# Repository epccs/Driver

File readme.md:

# Driver Circuits

From <https://github.com/epccs/Driver/>

## Overview

This is a collection of circuit boards. If you have questions consider posting an issue.

[RPUbus](https://rpubus.org)

[OrderForm](https://rpubus.org/Order_Form.html)

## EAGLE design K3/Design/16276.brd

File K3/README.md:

# K3 Hardware

## Overview

This latching solenoid driver board has three half H-bridge and a common half H-bridge that can be used to discharge a (9V/12V/24V) capacitively stored charge into a latching Solenoid coil. A current limited (300mA pk) boost converter (MC34063A) is on board to build up the stored charge from a low voltage (5V) supply.

Latching solenoids are driven with a current pulse that should last a short duration. The pulse from this driver flows in a single coil (don't use with multi-coil solenoids) and establishes a magnetic field that throws the solenoid into either a SET position or a RESET position. The pulse duration hopefully avoids overheating the coils. The Laplace force will not happen unless another magnetic field is present to act on, and will not convert electrical power into mechanical unless the force results in motion. The thrown solenoid also has a back emf in the driving coil.

## Inputs/Outputs/Functions

```
        Boost converter with 300mA pk input current limit.
        Boost leaves 200mA of a USB input for an Uno or ilk.
        Capacitor holds a charge for latching.
```

## Uses

```
        Single Coil Latching solenoids.
        Single Coil Latching relay.
```

# Table Of Contents

1. [Status](#status)
2. [Design](#design)
3. [Bill of Materials](#bill-of-materials)
4. [How To Use](#how-to-use)

# Status

[Options](#bill-of-materials)

```
        ^2  Done: Design, Layout, BOM, Review*, Order Boards, Assembly, Testing,
            WIP: Evaluation.
            Todo:   
            *during review the Design may change without changing the revision.
            Remove the parts that allow boost to connect to plug, just connect it with option to cut jumper.
            Use E3 to enable current source used to test for bridge short (save some power).
            Ship with C2 on pluggable header though I recommend soldering it when the current pulse is much over an Amp.
            location: 2017-3-30 Bench /w RPUno^6, RPUadpt^5.
                      2017-4-17 SxSXWall Encl /w RPUno^5, RPUadpt^4, SLP003-12U, 12V battery.

        ^1  Done: Design, Layout, BOM, Review*, Order Boards, Assembly, Testing, Evaluation.
            location: 2016-2-5 SxSXWall Encl /w RPUno^5, RPUadpt^4, SLP003-12U, 12V battery.
                      2016-4-17 Bench.
            
        ^0  location: 2016-12-1 SWall Encl /w RPUno^4, RPUadpt^4, SLP003-12U, 12V battery.
                      2016-2-4 removed, waiting in scrap bin.
                      2017-3-28 scraped (parts used on ^2).
```

Debugging and fixing problems i.e. [Schooling](./Schooling/)

Setup and methods used for [Evaluation](./Evaluation/)

# Design

The board is 0.063 thick, FR4, two layer, 1 oz copper with ENIG (gold) finish.

## Electrical Parameters (Typical)

```
input SUPPLY guidance: 4V to 7V
TBD (it is OSH)
```

## Mounting

```
        DIN rail
```

## Electrical Schematic

## Testing

Check correct assembly and function with [Testing](./Testing/)

# Bill of Materials

The BOM is a CVS file(s), import it into a spreadsheet program like LibreOffice Calc (or Excel), or use a text editor.

Option | BOM's included
----- | ----- 
A. | [BRD] 
Z. | [BRD] [SMD] [HDR] [PLUG] [DIN]

[BRD]: ./Design/16276BRD,BOM.csv
[SMD]: ./Design/16276SMD,BOM.csv
[HDR]: ./Design/16276HDR,BOM.csv
[PLUG]: ./Design/16276PLUG,BOM.csv
[DIN]: ./Design/16276DIN,BOM.csv

[Available](https://rpubus.org/Order_Form.html)

# How To Use

First a word about Latching Solenoids and Relays. They latch, so once a SET pulse is sent the physical part stays set until a RESET pulse is sent, even if power is lost. It is normally a good idea to send a reset pulse to each latch after power up to get them into a known state.

Latching Solenoids cost more but they use no power after latched, Energized DC circuits corroded quickly. 

The set pulse applies a voltage to the coil and produces a current in a direction that will cause the Laplace force to move the solenoid into that physical location. The reset pulse applies an opposite polarity to the coil. Once in the location some other force (spring, permanent magnet, air pressure... ), will hold the solenoid in that place.

For this circuit, the idea is to use one of the E3, nE2, or nE3 to DISABLE. Then change A0, A1, A2. Once A0 ... A2 have been selected the action happens when E3, nE2, and nE3 are all set active. Use the following settings:  

```
         A0 A1 A2 E3 nE2 nE1 : DESC
         X  X  X  0V X   X   : ALL DISABLED
         X  X  X  X  5V  X   : ALL DISABLED
         X  X  X  X  X   5V  : ALL DISABLED
         X  X  X  5V X   X   : ENABLE 17mA
         5V 0V 0V 5V 0V  0V  : BOOST
         0V 5V 0V 5V 0V  0V  : SET K1
         5V 5V 0V 5V 0V  0V  : RESET K1
         0V 0V 5V 5V 0V  0V  : SET K2
         5V 0V 5V 5V 0V  0V  : RESET K2
         0V 5V 5V 5V 0V  0V  : SET K3
         5V 5V 5V 5V 0V  0V  : RESET K3
```

Before a pulse can be sent the boost converter has to build a charge. Once E3 is active a 17mA current source will build up some voltage in the storage capacitor. When this is enough (somewhere between 1.2V to 2.2V) to allow the boost converter to turn on it will turn on a PMOS device to let power through and turn on the converter. If a bridge has failed then neither the PMOS or the converter will turn on (but the test current will keep flowing until E3 is disabled). If a charge does build up (as it should) then a pulse can be applied to set/reset one of the solenoids by writing A0, A1, and A2 inputs simultaneously (e.g. a port operation). It is also possible to change one pin at a time with the digitalWrite() function (from Wiring), but care must be taken to have the logic disabled (i.e. E3 = 0V) while selecting the A0/A1/A2 lines otherwise the charge is sent to the first line that changed while making the selection.

I've been using CAT5 pair to wire the coils. At nearly 5 Amps peak that may be risky but for a short duration pulse the CAT5 pair seems to work (your mileage may vary, but it is cheap and the twisted pair helps keep the pulse from generating EMI). 

When the pulse is sent the boost converter is turned off so only the charge in the storage capacitor (2200uF) is sent, this should keep things within the safe operating area of the output MOSFETS as long as at least 4 Ohms of resistance is between the bridges. Anything less than 4 Ohms allows excessive current and will eventually lead to a failure. For reference, 10 meters of CAT5 has less than 1.7 Ohm.

Solenoid options

* Orbit 58874N, 58874Z, 91592, 96120 Latching Solenoid valve (seems to work OK with 24V 50mSec pulse from 2200uF).
* Orbit 57861 Latching Solenoid replacement for AC operated valve (I do not have this, it plugs into Orbits 24V controls but most others are are using 9V).
* DIG S-305DC Solenoid & Adapters (http://www.digcorp.com/professional-irrigation-products/s-305dc-9-vdc-solenoid-adapters).
* Hunter 458200 Latching Solenoid for AC operated valve (e.g. ICV201GDC and ilk, but I do not have one, probably 9V pulse)
* Irritrol DCL Latching Solenoid for AC operated valve (e.g. 2400S and ilk, but I do not have one, probably 9V pulse)

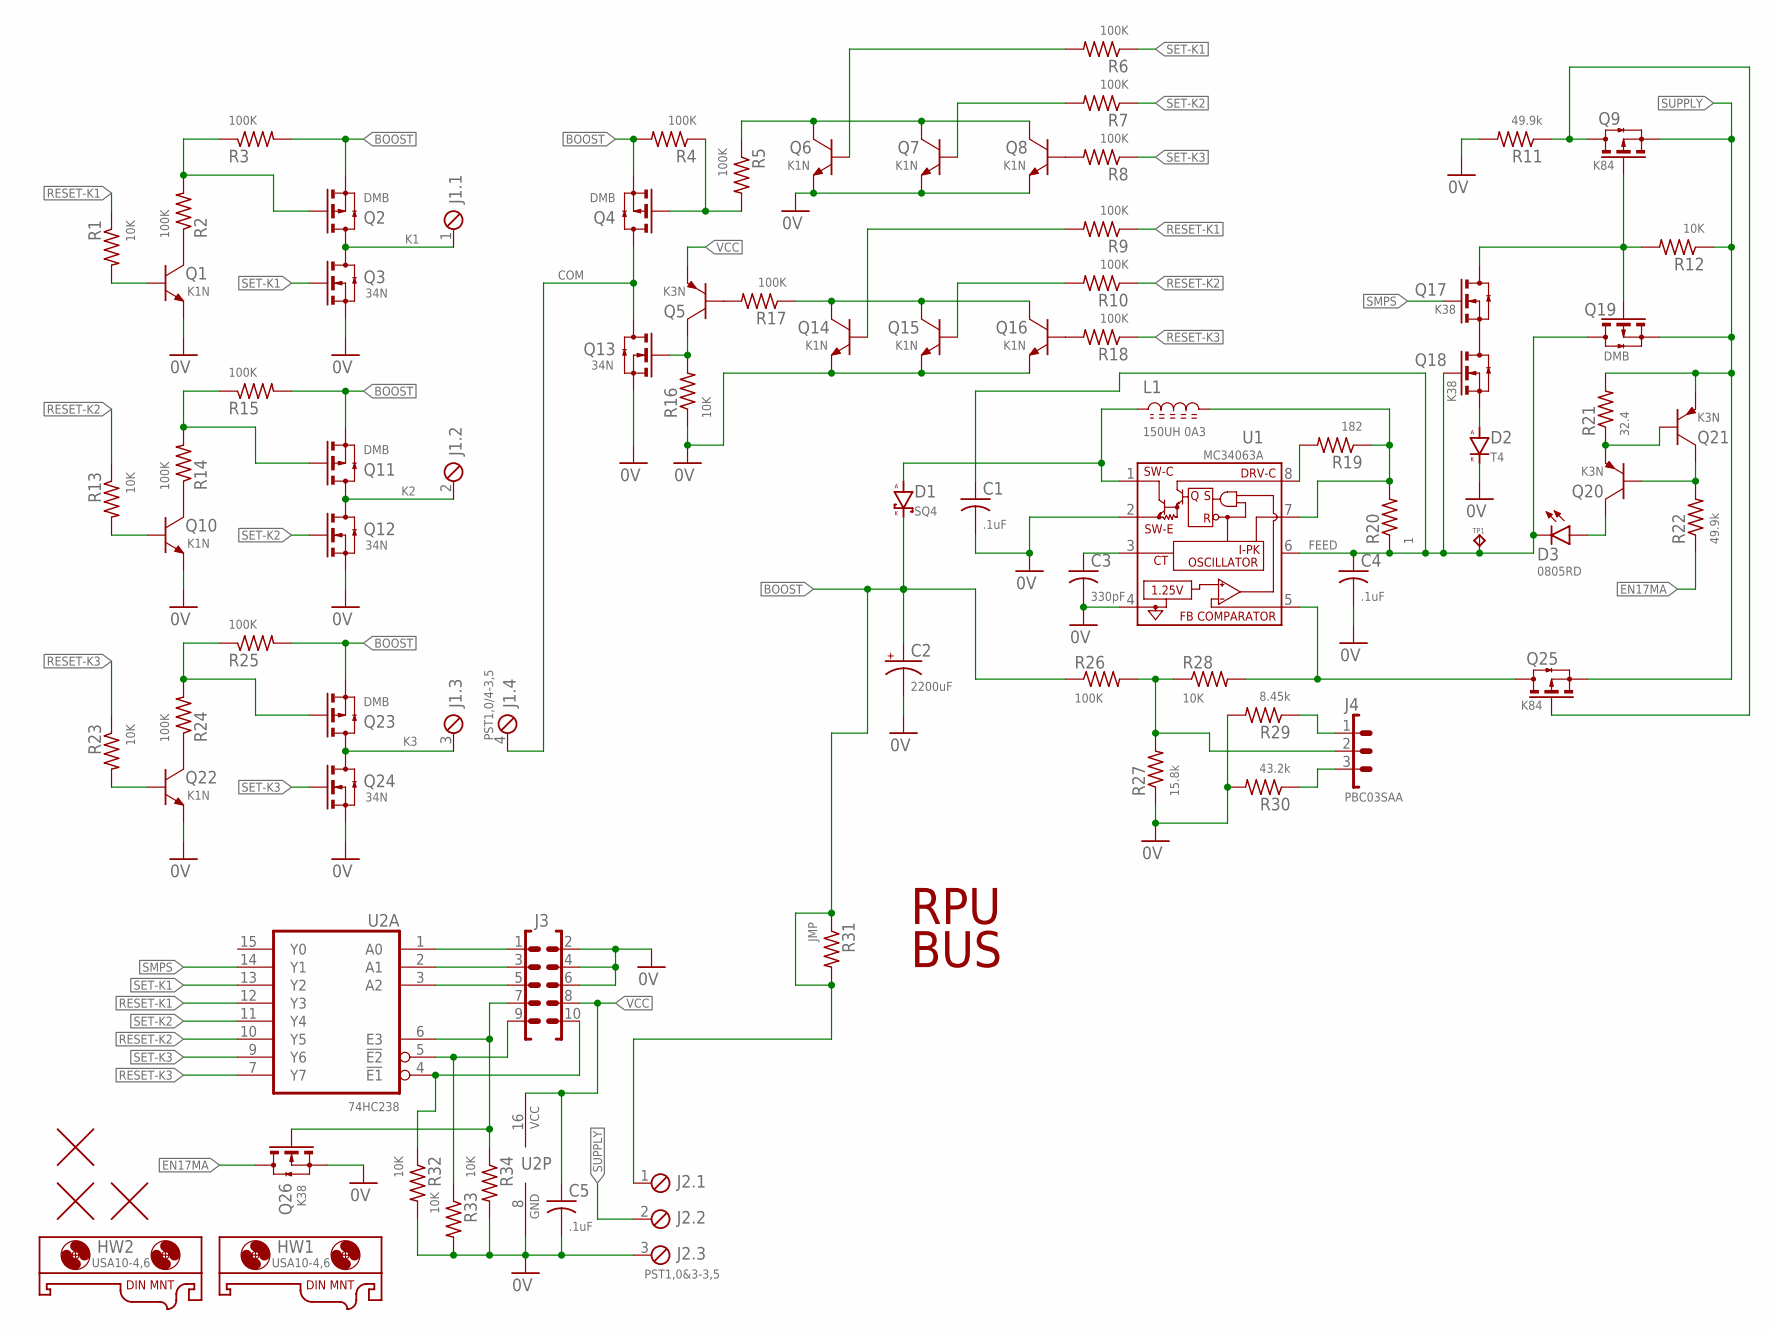
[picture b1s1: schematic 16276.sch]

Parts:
C1, C4, C5: .1uF; C0603(1608)
C2: 2200uF; E7,5-18
C3: 330pF; C0603(1608)
D1: SQ4; SMA
D2: T4; SOD123
D3: 0805RD; C0805(2012)
HW1, HW2: USA10-4,6; USA10
J1: PST1,0/4-3,5; MCV4
J2: PST1,0&3-3,5; MCV3
J3: 2X5
J4: PBC03SAA; 1X3
L1: 150UH 0A3; L2626
Q1, Q6, Q7, Q8, Q10, Q14, Q15, Q16, Q22: K1N; SOT23
Q2, Q4, Q11, Q19, Q23: DMB; SOT23
Q3, Q12, Q13, Q24: 34N; SOT23
Q5, Q20, Q21: K3N; SOT23
Q9, Q25: K84; SOT23
Q17, Q18, Q26: K38; SOT23
R1, R12, R13, R16, R23, R28, R32, R33, R34: 10K; C0805(2012)
R2, R3, R4, R5, R6, R7, R8, R9, R10, R14, R15, R17, R18, R24, R25, R26: 100K; C0805(2012)
R11, R22: 49.9k; C0805(2012)
R19: 182; C0805(2012)
R20: 1; C1210(3225)
R21: 32.4; C0805(2012)
R27: 15.8k; C0805(2012)
R29: 8.45k; C0805(2012)
R30: 43.2k; C0805(2012)
R31: JMP; C0805(2012)
TP1: TPPAD1-08; P1-08
U1: MC34063A; SOIC8
U2: 74HC238; 16SOIC
U$2, U$3, U$4: FIDUCIAL1.27; FIDUCIAL-1.27

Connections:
0V: C1.2, C2.-, C3.2, C4.2, C5.2, D2.C (K), J2.3, J3.2, J3.4, J3.6, Q1.E, Q3.2(S) (S), Q6.E, Q7.E, Q8.E, Q10.E, Q12.2(S) (S), Q13.2(S) (S), Q14.E, Q15.E, Q16.E, Q22.E, Q24.2(S) (S), Q26.2(S) (S), R11.2, R16.1, R27.1, R29.2, R30.2, R32.2, R33.2, R34.2, U1.2 (SW-E), U1.4 (GND), U2.8 (GND)
!E1: J3.10, R32.1, U2.4 (!E1)
!E2: J3.9, R33.1, U2.5 (!E2)
A0: J3.1, U2.1 (A0)
A1: J3.3, U2.2 (A1)
A2: J3.5, U2.3 (A2)
BOOST: C2.+, D1.K, J2.1, Q2.2(S) (S), Q4.2(S) (S), Q11.2(S) (S), Q23.2(S) (S), R3.2, R4.2, R15.2, R25.2, R26.1, R31.1, R31.2
COM: J1.4, Q4.3(D) (D), Q13.3(D) (D)
E3: J3.7, Q26.1(G) (G), R34.1, U2.6 (E3)
EN17MA: Q26.3(D) (D), R22.1
FEED: C1.1, C4.1, D3.K, Q18.1(G) (G), Q19.3(D) (D), R20.1, TP1.TP, U1.6 (VCC)
K1: J1.1, Q2.3(D) (D), Q3.3(D) (D)
K2: J1.2, Q11.3(D) (D), Q12.3(D) (D)
K3: J1.3, Q23.3(D) (D), Q24.3(D) (D)
unnamed: Q9.3(D) (D), Q25.1(G) (G), R11.1
unnamed: Q23.1(G) (G), R24.2, R25.1
unnamed: Q22.C, R24.1
unnamed: Q22.B, R23.2
unnamed: Q17.2(S) (S), Q18.3(D) (D)
unnamed: Q25.3(D) (D), R28.2, U1.5 (FB)
unnamed: D2.A, Q18.2(S) (S)
unnamed: Q4.1(G) (G), R4.1, R5.2
unnamed: R19.2, U1.8 (DRV-C)
unnamed: L1.2, R19.1, R20.2, U1.7 (I-PK)
unnamed: D1.A, L1.1, U1.1 (SW-C)
unnamed: C3.1, U1.3 (CT)
unnamed: Q5.C, Q13.1(G) (G), R16.2
unnamed: Q9.1(G) (G), Q17.3(D) (D), Q19.1(G) (G), R12.2
unnamed: J4.2, R26.2, R27.2, R28.1
unnamed: Q6.C, Q7.C, Q8.C, R5.1
unnamed: Q6.B, R6.2
unnamed: Q8.B, R8.2
unnamed: Q2.1(G) (G), R2.2, R3.1
unnamed: Q1.C, R2.1
unnamed: Q1.B, R1.2
unnamed: Q11.1(G) (G), R14.2, R15.1
unnamed: Q10.C, R14.1
unnamed: Q10.B, R13.2
unnamed: Q7.B, R7.2
unnamed: Q5.B, R17.2
unnamed: Q14.C, Q15.C, Q16.C, R17.1
unnamed: Q14.B, R9.2
unnamed: Q15.B, R10.2
unnamed: D3.A, Q20.C
unnamed: Q16.B, R18.2
unnamed: J4.3, R30.1
unnamed: J4.1, R29.1
unnamed: Q20.E, Q21.B, R21.1
unnamed: Q20.B, Q21.C, R22.2
RESET-K1: R1.1, R9.1, U2.12 (Y3)
RESET-K2: R10.1, R13.1, U2.10 (Y5)
RESET-K3: R18.1, R23.1, U2.7 (Y7)
SET-K1: Q3.1(G) (G), R6.1, U2.13 (Y2)
SET-K2: Q12.1(G) (G), R7.1, U2.11 (Y4)
SET-K3: Q24.1(G) (G), R8.1, U2.9 (Y6)
SMPS: Q17.1(G) (G), U2.14 (Y1)
SUPPLY: J2.2, Q9.2(S) (S), Q19.2(S) (S), Q21.E, Q25.2(S) (S), R12.1, R21.2
VCC: C5.1, J3.8, Q5.E, U2.16 (VCC)

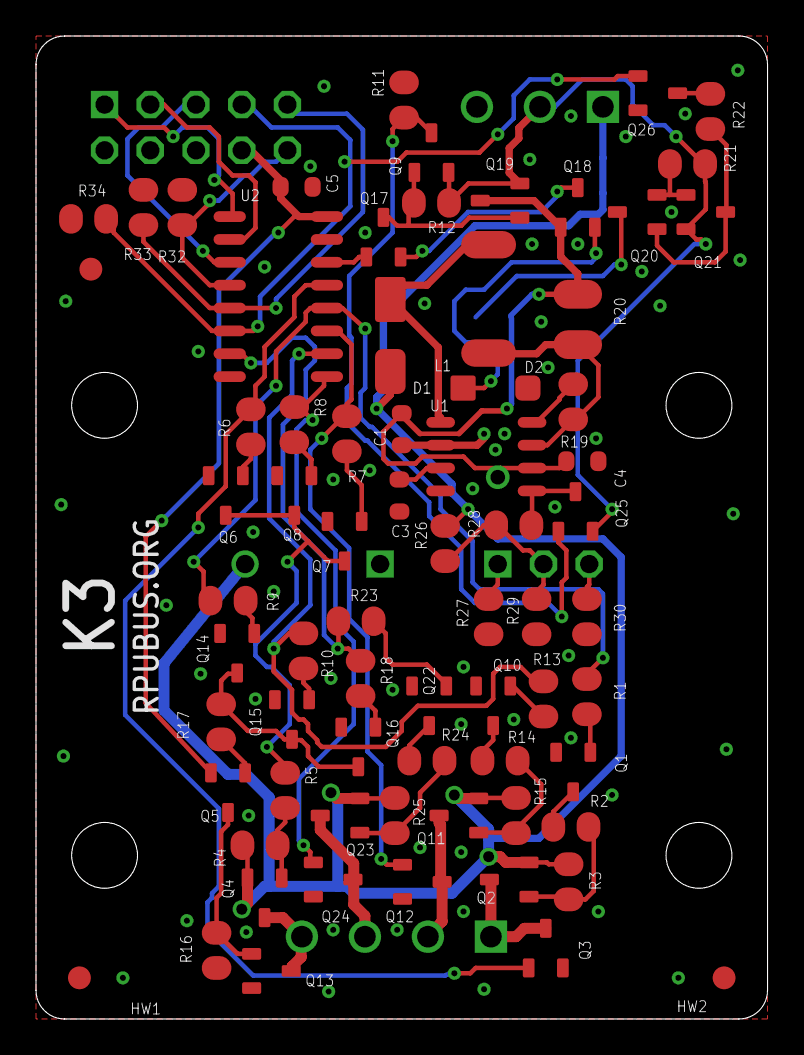
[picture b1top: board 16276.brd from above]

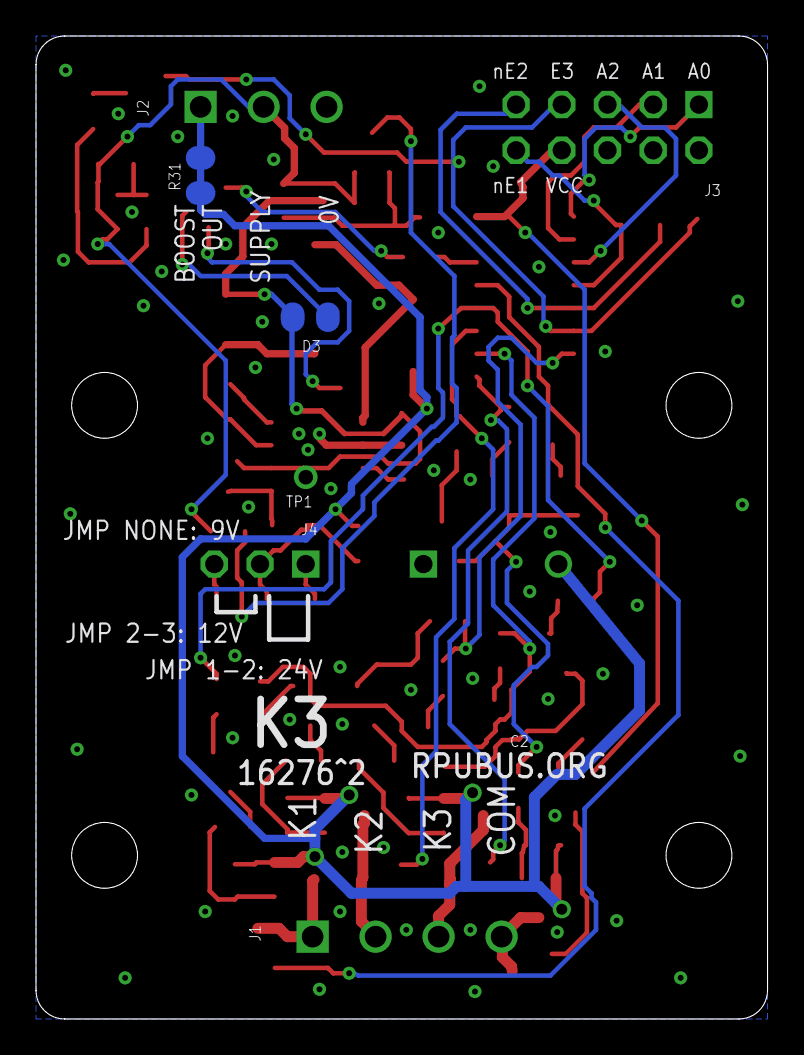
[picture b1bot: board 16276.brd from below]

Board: 2 copper layers, 40.6 x 54.6 mm, 81 parts (8 on the bottom side), 58 nets.

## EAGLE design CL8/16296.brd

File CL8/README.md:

# CL8 Hardware

## Overview

Select 1 of 8 Current Loop sensors. The sellected current  path returns current flow to a common termination (sense) resistor.

## Inputs/Outputs/Functions

```
        Input a current loop source
        Output to a loop termination resistor
        Ditital control using a 74HC238 logic IC
        Multiplex 1 of 8 sensors with a supply (current source).
```

## Uses

```
        Select one from several sensors (e.g. MT, LT, HT).
```

# Table Of Contents

1. [Status](#status)
2. [Design](#design)
3. [Bill of Materials](#bill-of-materials)
4. [How To Use](#how-to-use)

# Status

This was split out of Irrigate7 to try some ideas. The plan was to use this with the input capture (ICP3) on Irrigate7 to measure pulse timing from soil moisture sensors. However CL8 also works with regular current loops on the ADC inputs and can be used with RPUno. Irrigate7 with two pulse sensor inputs seems like a good idea, so this circuit will not be integrated back onto that board but can be used with it. 

```
        ^0  Done: Design, Layout, BOM, Review*, Order Boards, Assembly, 
            WIP: Testing (sort of on hold for now), 
            Todo: Evaluation.
            *during review the Design may change without changing the revision.
            location: 2016-11-12 Bench.
```

Debugging and fixing problems i.e. [Schooling](./Schooling/)

Setup and methods used for [Evaluation](./Evaluation/)

# Design

The board is 0.063 thick, FR4, two layer, 1 oz copper with ENIG (gold) finish.

## Electrical Parameters (Typical)

```
input SUPPLY guidance: 4V to 7V
TBD (it is OSH)
```

## Mounting

```
        DIN rail
```

## Electrical Schematic

## Testing

Check correct assembly and function with [Testing](./Testing/)

# Bill of Materials

Import the [BOM](./Design/16296,BOM.csv) into LibreOffice Calc (or Excel) with semicolon separated values, or use a text editor.

# How To Use

For this circuit, the idea is to set one of the E3, nE2, or nE3 to DISABLE. Then change A0, A1, A2. Once A0 ... A2 have been selected the action happens when E3, nE2, and nE3 are all set active. Use the following settings:  

```
         A0 A1 A2 E3 nE2 nE1 : DESC
         X  X  X  0V X   X   : ALL DISABLED
         X  X  X  X  5V  X   : ALL DISABLED
         X  X  X  X  X   5V  : ALL DISABLED
         0V 0V 0V 5V 0V  0V  : LS0 SELECTED
         5V 0V 0V 5V 0V  0V  : LS1 SELECTED
         0V 5V 0V 5V 0V  0V  : LS2 SELECTED
         5V 5V 0V 5V 0V  0V  : LS3 SELECTED
         0V 0V 5V 5V 0V  0V  : LS4 SELECTED
         5V 0V 5V 5V 0V  0V  : LS5 SELECTED
         0V 5V 5V 5V 0V  0V  : LS6 SELECTED
         5V 5V 5V 5V 0V  0V  : LS7 SELECTED
```

I have some capacitive sensors (MT, LT and HT) that operate a pulsed current loop by transmiting a 3mA or 10mA signal depending on the output of a 555 type timer. The signal is converted into a voltage pulse by the loops sense resistor that dubles as a transmission line termination resistor. This board is used to direct power (on RPUno use the 17mA pin of the FT/PULSE connector) to one of the sensors and then return the selected sensors transmitted signal on a common circuit node (LT) that should be connected to the termination resistor (on RPUno use the PL pin of the FT/PULSE connector).

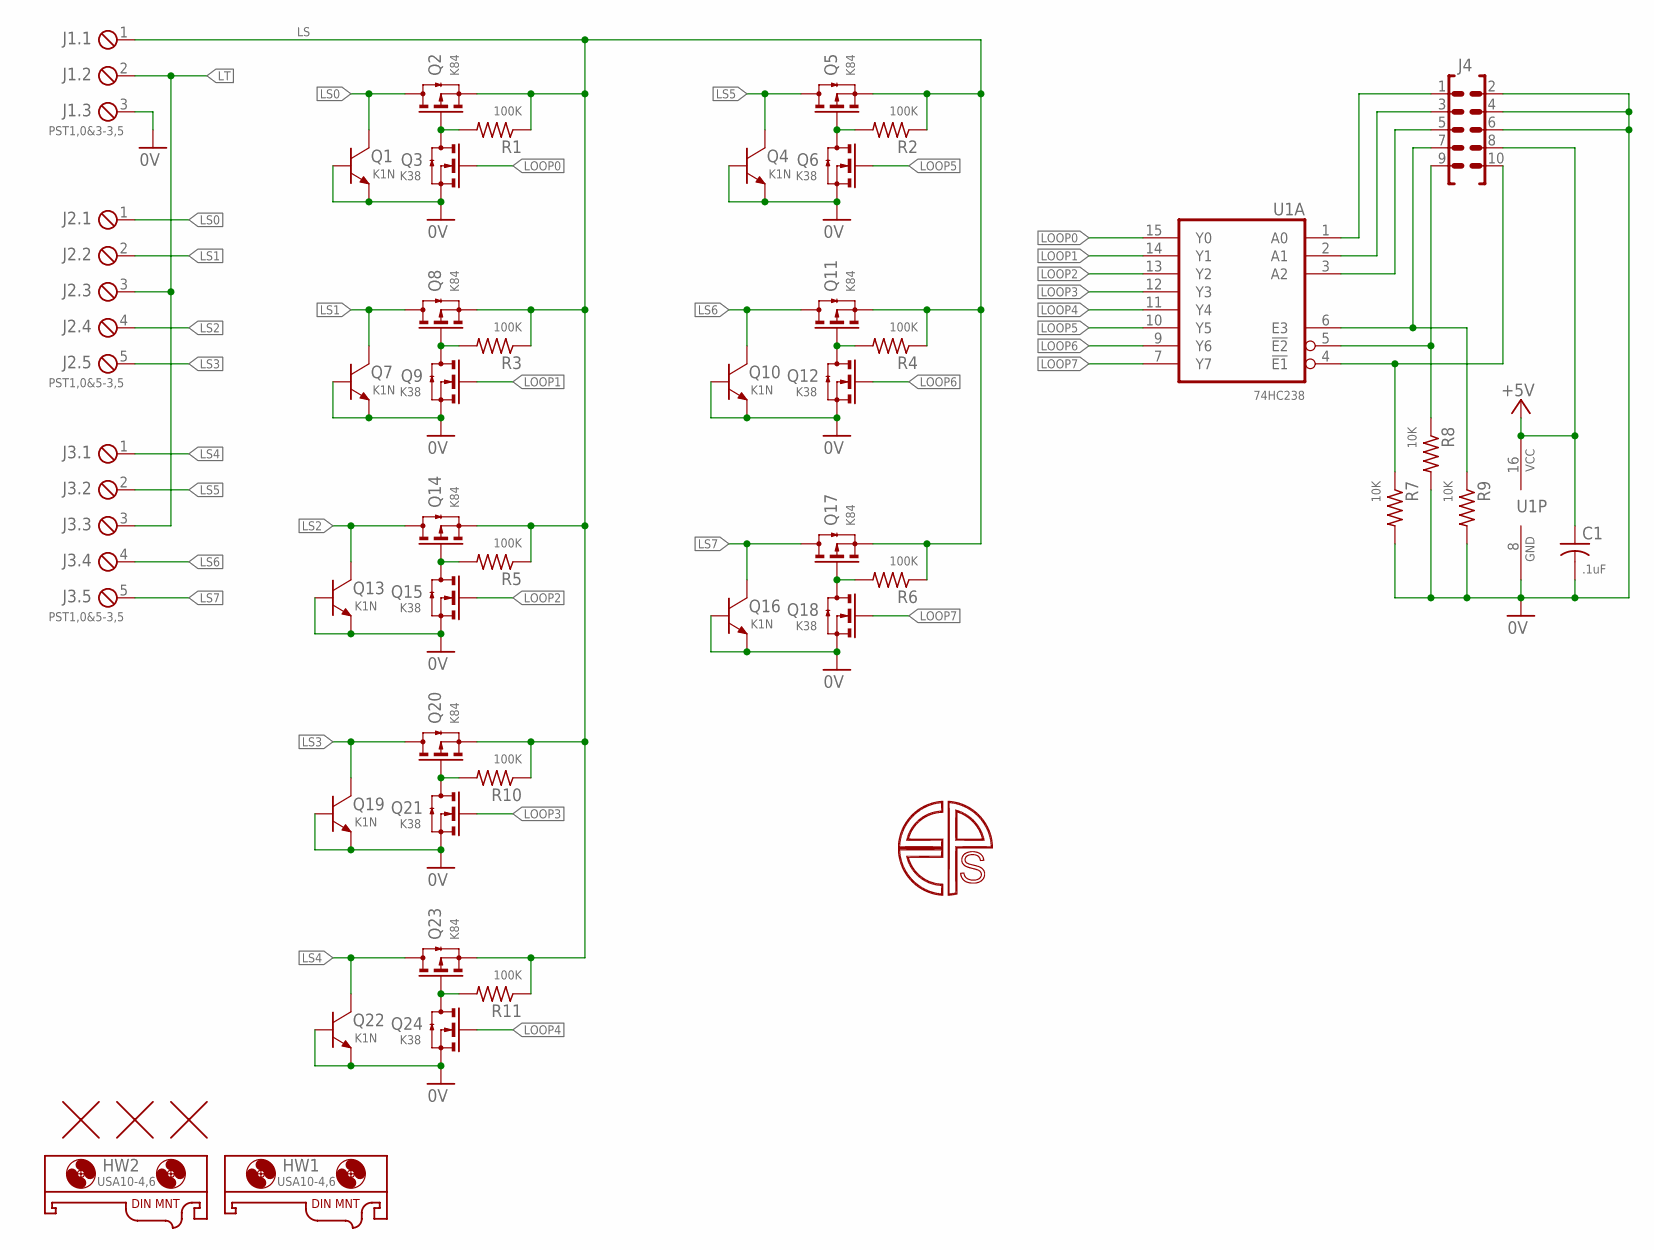
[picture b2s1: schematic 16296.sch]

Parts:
C1: .1uF; C0603(1608)
HW1, HW2: USA10-4,6; USA10
J1: PST1,0&3-3,5; MCV3
J2, J3: PST1,0&5-3,5; MCV5
J4: 2X5
Q1, Q4, Q7, Q10, Q13, Q16, Q19, Q22: K1N; SOT23
Q2, Q5, Q8, Q11, Q14, Q17, Q20, Q23: K84; SOT23
Q3, Q6, Q9, Q12, Q15, Q18, Q21, Q24: K38; SOT23
R1, R2, R3, R4, R5, R6, R10, R11: 100K; C0805(2012)
R7, R8, R9: 10K; C0805(2012)
U1: 74HC238; 16SOIC
U$2, U$3, U$4: FIDUCIAL1.27; FIDUCIAL-1.27

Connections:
0V: C1.2, J1.3, J4.2, J4.4, J4.6, Q1.B, Q1.E, Q3.2(S) (S), Q4.B, Q4.E, Q6.2(S) (S), Q7.B, Q7.E, Q9.2(S) (S), Q10.B, Q10.E, Q12.2(S) (S), Q13.B, Q13.E, Q15.2(S) (S), Q16.B, Q16.E, Q18.2(S) (S), Q19.B, Q19.E, Q21.2(S) (S), Q22.B, Q22.E, Q24.2(S) (S), R7.2, R8.2, R9.2, U1.8 (GND)
!E1: J4.10, R7.1, U1.4 (!E1)
!E2: J4.9, R8.1, U1.5 (!E2)
+5V: C1.1, J4.8, U1.16 (VCC)
A0: J4.1, U1.1 (A0)
A1: J4.3, U1.2 (A1)
A2: J4.5, U1.3 (A2)
E3: J4.7, R9.1, U1.6 (E3)
LOOP0: Q3.1(G) (G), U1.15 (Y0)
LOOP1: Q9.1(G) (G), U1.14 (Y1)
LOOP2: Q15.1(G) (G), U1.13 (Y2)
LOOP3: Q21.1(G) (G), U1.12 (Y3)
LOOP4: Q24.1(G) (G), U1.11 (Y4)
LOOP5: Q6.1(G) (G), U1.10 (Y5)
LOOP6: Q12.1(G) (G), U1.9 (Y6)
LOOP7: Q18.1(G) (G), U1.7 (Y7)
LS: J1.1, Q2.2(S) (S), Q5.2(S) (S), Q8.2(S) (S), Q11.2(S) (S), Q14.2(S) (S), Q17.2(S) (S), Q20.2(S) (S), Q23.2(S) (S), R1.1, R2.1, R3.1, R4.1, R5.1, R6.1, R10.1, R11.1
LS0: J2.1, Q1.C, Q2.3(D) (D)
LS1: J2.2, Q7.C, Q8.3(D) (D)
LS2: J2.4, Q13.C, Q14.3(D) (D)
LS3: J2.5, Q19.C, Q20.3(D) (D)
LS4: J3.1, Q22.C, Q23.3(D) (D)
LS5: J3.2, Q4.C, Q5.3(D) (D)
LS6: J3.4, Q10.C, Q11.3(D) (D)
LS7: J3.5, Q16.C, Q17.3(D) (D)
LT: J1.2, J2.3, J3.3
unnamed: Q5.1(G) (G), Q6.3(D) (D), R2.2
unnamed: Q8.1(G) (G), Q9.3(D) (D), R3.2
unnamed: Q11.1(G) (G), Q12.3(D) (D), R4.2
unnamed: Q14.1(G) (G), Q15.3(D) (D), R5.2
unnamed: Q17.1(G) (G), Q18.3(D) (D), R6.2
unnamed: Q20.1(G) (G), Q21.3(D) (D), R10.2
unnamed: Q23.1(G) (G), Q24.3(D) (D), R11.2
unnamed: Q2.1(G) (G), Q3.3(D) (D), R1.2

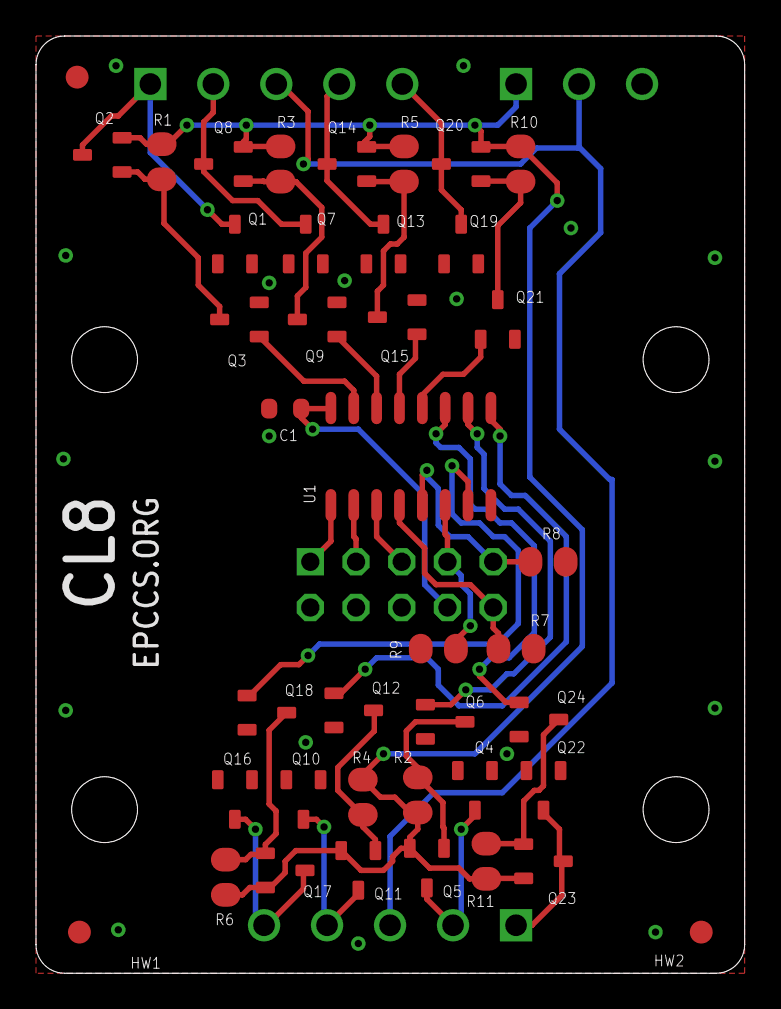
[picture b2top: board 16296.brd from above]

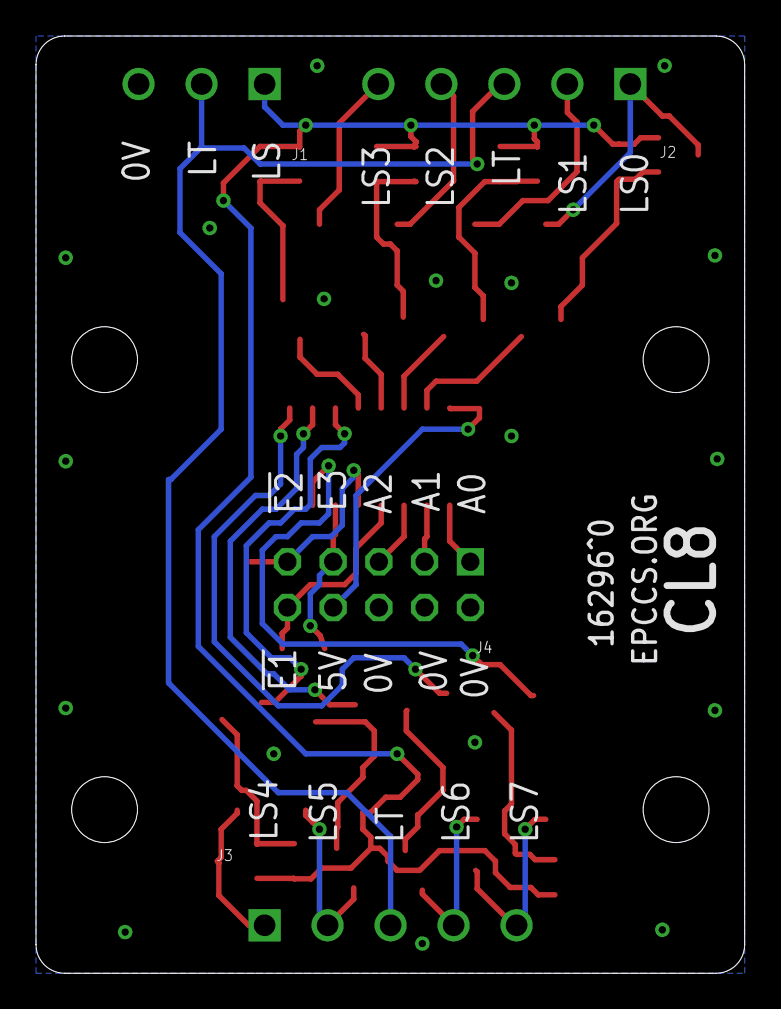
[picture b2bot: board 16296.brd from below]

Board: 2 copper layers, 39.4 x 52.1 mm, 46 parts (4 on the bottom side), 34 nets.

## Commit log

2016-11-17 :space_invader: Added .gitattributes
2016-11-17 init with K3
2016-11-17 CL8: add loop select board
2016-11-30 K3: add testing and evaluation
    try some markdown and reorg
2016-11-30 K3: eval video link
2017-01-27 K3: add example
2017-01-28 K3: fix link to test
2017-01-28 K3: use E3 input to turn on curr source
    that test for bridge shorts
2017-01-30 K3: ^1 assembly
2017-01-31 K3: Q28 source and drain need flipped
2017-02-05 K3: evaluation ^1 replaces ^0 in the SWall Encl
2017-02-06 K3: ^2 review
2017-02-08 K3: readme
2017-03-05 bad eagle
2017-03-30 K3: ^2 evaluation
2017-04-02 K3: ^2 bench evaluation
2017-04-03 ICSP: levle shift for ICSP tool
    this was previous work on my old web site, it is a solid way to do levle
    shift for an ICSP tool
2017-04-08 ICSP: testing
    IOFF is more important than I am saying
2017-04-18 K3: ^2 outside encl evaluation
2017-04-19 K3: first parts for Tindie store
2017-04-19 K3: in tindie store
2017-04-19 K3: more links to Tindie
2017-04-20 ICSP: ^1 assy, testing and evaluation
2017-04-20 ICSP: status icon
2017-04-20 ICSP: link to the ISP sketch
2017-04-21 ICSP: is on tindie
2017-04-26 ICSP: bom csv format can look nice on Github
2017-04-26 that csv did not work
2017-04-26 ICSP: csv is for comma separated data not semicolon separated data
2017-04-27 K3: bom is comma seperated data
2017-04-27 K3: bom csv has Illegal quoting
2017-04-27 K3: bom csv has more Illegal quoting
2017-04-30 K3: ^2 evaluation with the three garden zones
2017-07-20 K3: use 35V 2.2mF cap rather than the 63V
2018-03-13 USBuart: init
    plan is to kill RPUftdi and use this with RPUadpt when I want a USB
2018-03-16 USBuart: bom
2018-03-17 PVsw: init
2018-03-18 PVsw: ^0 reviewing
2018-03-29 add pvsw board to readme
2018-06-10 K3: eval with RPUno^9
2018-06-10 K3: + eval with RPUno^9
2018-07-19 USBuart: ^0 assembly
2018-07-20 USBuart: ^0 testing
2018-07-21 PVsw: ^0 assembly
2018-08-12 USBuart: ^1 needs review
2018-09-09 485tx_en: init
2018-09-09 485tx_en: reviewing
2018-09-09 485tx_en: I am, guess we were me, myself, and I
2018-09-29 USBuart: ^1 reviewing
2018-09-29 485tx_en: ^0 reviewing
2018-10-19 USBuart: ^1 assembly
2018-10-20 USBuart: ^1 testing
2018-10-20 USBuart: ^1 evaluation wip
2018-10-21 485tx_en: ^0 assembly
2018-10-21 485tx_en: ^0 testing
2018-10-23 485tx_en: ^0 evaluating
2018-10-30 485tx_en: ^1 review
2019-02-16 CL8: remove
2019-02-16 link to order form from bom after options
2019-02-16 K3: bom breakout z option is in stock atm
2019-02-18 K3: remove old bom notes
2019-04-16 PWM: init
2019-04-22 ICSP: ^2 layout
    an R-Pi is going to be used as the host
2019-04-24 collection names are enough, ICSP: how to use
2019-05-04 ICSP: and PWM boards on order
2019-05-06 show some status icons and rm form link
2019-05-13 PWM: add i2c cable to bom
2019-05-14 ICSP: ^2 assemby top side
2019-05-15 ICSP: ^2 testing started
2019-05-17 ICSP: bootload py script
2019-05-17 ICSP: ^2 evaluation started, serial bootloading checked
2019-05-18 ICSP: linuxspi works, but ^2 board has an SPI issue
    also avrdude package on Raspian needs linuxspi updates from facchinm/avrdude.
2019-05-18 Evaluation: done, md tag for images
2019-06-12 ICSP: ^3 reviewing
2019-10-11 ICSP: export gpio25 before avrdude uses it
2020-08-11 CCsm: hardware
2020-08-12 CCmid: init
    CCsm is 20223
2020-08-12 CCmid: layout and bom done, reviewing
2020-08-15 Buck: layout, bom is wip
2020-08-15 Buck: bom done, reviewing

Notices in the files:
parts and their libraries:
H-Fiducial: Copyright (C) 2013 Ronald Steven Sutherland
under the terms of the GNU Free Documentation License, Version 1.2 or
any later version published by the Free Software Foundation; with no
HW-DINMnt: Released under the Creative Commons
Attribution Share-Alike 3.0 License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
